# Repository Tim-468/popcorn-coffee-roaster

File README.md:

# popcorn-coffee-roaster

Turn your popcorn machine into a temperature-controlled coffee roaster

## TODO

- Test 24 V supply from AC/DC converter
- Remove diode bridge (or not?)
- Put a terminal block rated for Class II >= 340 V for 3x AC mains cables and 2x 24 V fan supply cables
- Somehow fit the WROOM32-D board inside the case (a right angle PCB header could maybe do it)
- Take photos to show required modifications and the assembly
- Test 1.5 mm diameter hole for 1 mm2 stranded wire

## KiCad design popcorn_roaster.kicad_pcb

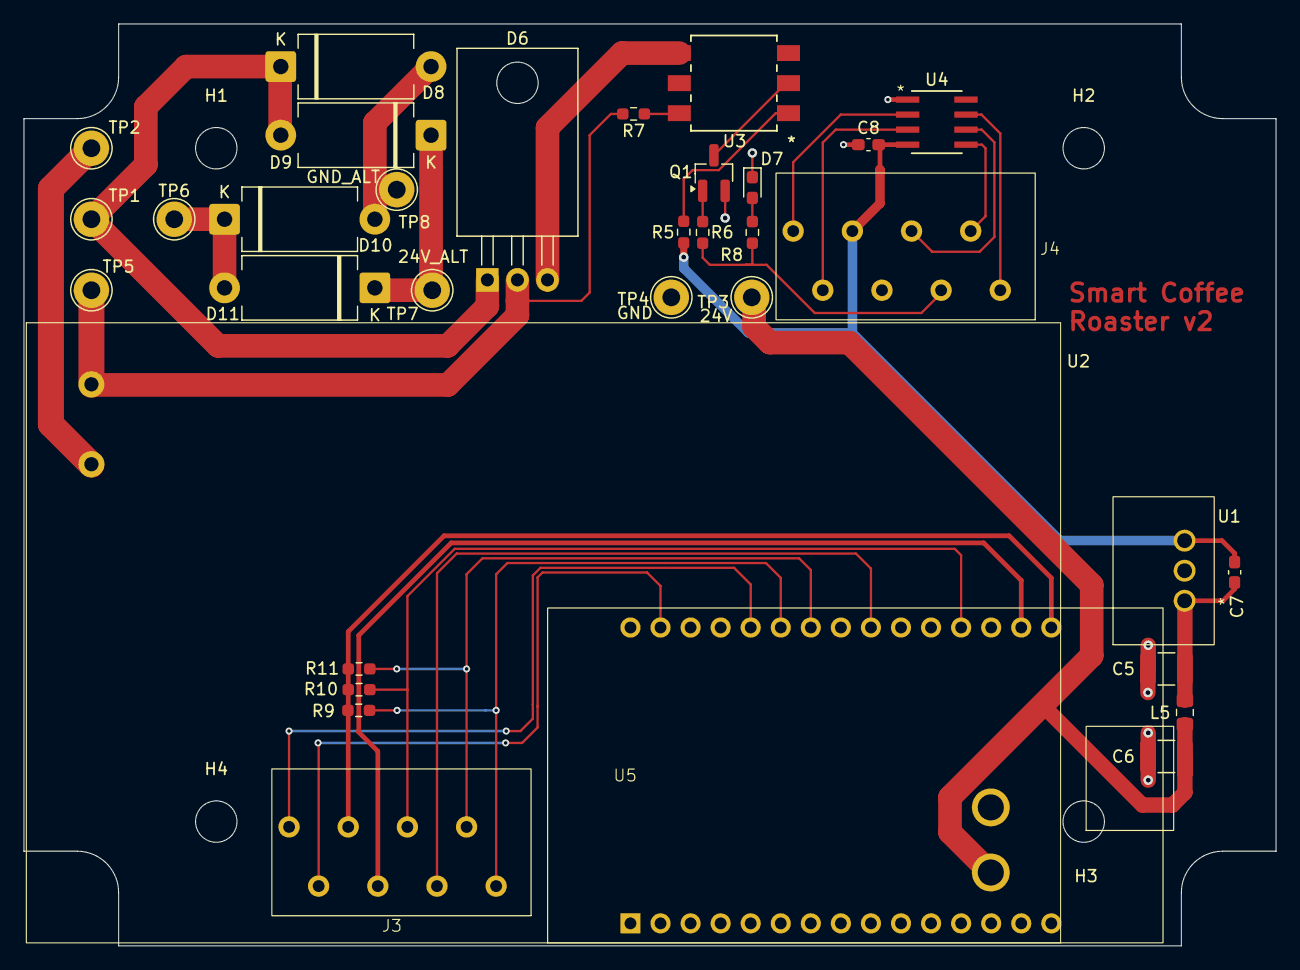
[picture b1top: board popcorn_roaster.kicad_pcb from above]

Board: 2 copper layers, 105.8 x 77.9 mm, 38 parts (0 on the bottom side), 30 nets.

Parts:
C5, C6: 10uF; C_1210_3225Metric_Pad1.33x2.70mm_HandSolder
C7: 1nF; C_0603_1608Metric_Pad1.08x0.95mm_HandSolder
C8: 100nF; C_0603_1608Metric_Pad1.08x0.95mm_HandSolder
D6: BTA24-600BWRG; TO-220-3_Horizontal_TabDown
D7: Green; LED_0603_1608Metric_Pad1.05x0.95mm_HandSolder
D8, D9, D10, D11: 1N5401; D_DO-201_P12.70mm_Horizontal
H1, H2, H3, H4: MountingHole; MountingHole_3.5mm
J3, J4: 1990067_PHOENIX
L5: 100uH; L_0805_2012Metric_Pad1.15x1.40mm_HandSolder
Q1: BC847B; SOT-23_Handsoldering
R5, R6: 100R; R_0603_1608Metric_Pad0.98x0.95mm_HandSolder
R7: 10K0; R_0603_1608Metric_Pad0.98x0.95mm_HandSolder
R8, R9, R10, R11: 10K; R_0603_1608Metric_Pad0.98x0.95mm_HandSolder
TP1, TP2, TP3, TP4, TP5, TP6, TP7, TP8: TestPoint; TestPoint_THTPad_D3.0mm_Drill1.5mm
U1: R-78K3.3-0.5; R-78K3.3-0.5_RECOM
U2: IRM-45-24; IRM60_MEANWELL
U3: MOC3063S; SOP6P254_730X1016X460L100X120
U4: MAX31855; SOIC127P600X175-8
U5: ESP32-WROOM32D-DEVBOARD

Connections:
+3V3: C7.2, C8.2, J4.3, R5.1, U1.3 (Vout), U4.4 (VCC)
+3V3_mc: J3.3, R9.2, R10.2, R11.2, U5.16 (3V3)
+24V: C6.1, L5.1, TP3.1, U2.3 (Vout+)
/Smart Roaster/HEAT_ON: J4.6, R6.1, R8.1
/Smart Roaster/HEAT_ON_mc: J3.6, U5.22 (D17)
/Smart Roaster/N (blue): TP2.1, U2.2 (AC_N)
/Smart Roaster/POCI: J4.8, U4.7 (SO)
/Smart Roaster/POCI_mc: J3.8, R9.1, U5.25 (D19)
/Smart Roaster/RESERVED1_mc: J3.1, U5.26 (D21)
/Smart Roaster/RESERVED2_mc: J3.2, U5.29 (D22)
/Smart Roaster/SCK: J4.7, U4.5 (SCK)
/Smart Roaster/SCK_mc: J3.7, R11.1, U5.24 (D18)
/Smart Roaster/TC+: J4.2, U4.3 (T+)
/Smart Roaster/TC-: J4.1, U4.2 (T-)
/Smart Roaster/heat_black: D6.2 (A2), R7.2, TP5.1, U2.1 (AC_L)
/Smart Roaster/heat_blue: D6.1 (A1), D8.1 (K), D9.2 (A), TP1.1
/Smart Roaster/heat_white: D10.1 (K), D11.2 (A), TP6.1
/Smart Roaster/nCS: J4.5, U4.6 (nCS)
/Smart Roaster/nCS_mc: J3.5, R10.1, U5.19 (D2)
GND: C5.2, C6.2, C8.1, D7.1 (K), J4.4, Q1.2 (E), TP4.1, U1.2 (GND), U2.4 (Vout-), U4.1 (GND)
GND_mc: J3.4, U5.17 (GND)
unnamed: D6.3 (G), U3.4 (A1)
unnamed: D7.2 (A), R8.2
unnamed: D8.2 (A), D10.2 (A), TP8.1
unnamed: D9.1 (K), D11.1 (K), TP7.1
unnamed: Q1.1 (B), R6.2
unnamed: Q1.3 (C), U3.2 (C)
unnamed: C5.1, C7.1, L5.2, U1.1 (Vin)
unnamed: R7.1, U3.6 (A2)
unnamed: R5.2, U3.1 (A)

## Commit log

2025-11-28 Add .gitignore file
2025-11-28 Release v2
2025-11-28 Use larger package for capacitors
2025-11-28 Remove unnecessary mounting holes
2025-11-28 Add CHANGELOG.md
2025-11-28 Make test point holes larger (1.0 => 1.5 mm)
2025-11-28 Change order of 8-pin terminal block pins
2025-11-28 Add clearance rules for AC mains lines
2025-11-28 Remove duplicate silkscreen marking from SOP6P254_730X1016X460L100X120
2025-11-28 Add LICENSE.md
2025-11-28 Add TODOs in README.md
